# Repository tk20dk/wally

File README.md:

# Wally - CEC sniffer, sink and source emulator

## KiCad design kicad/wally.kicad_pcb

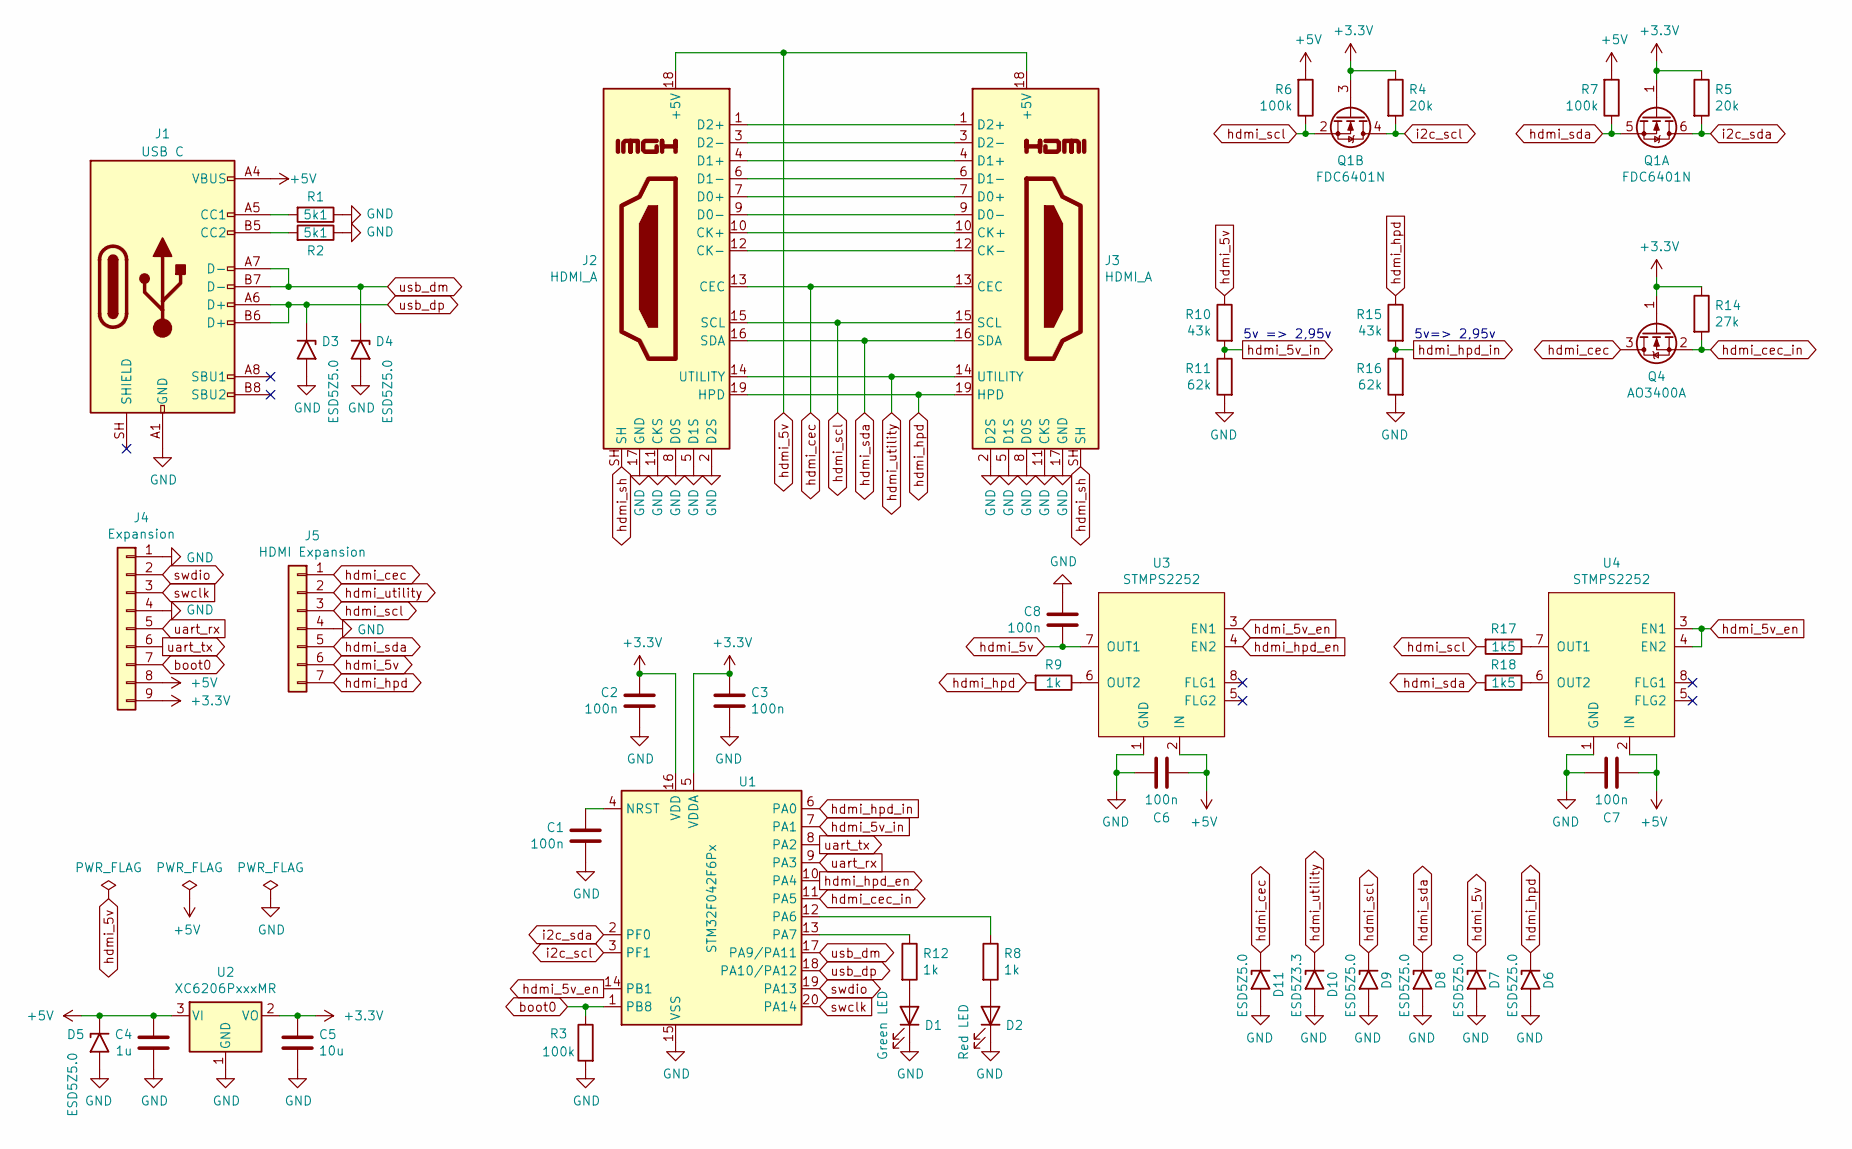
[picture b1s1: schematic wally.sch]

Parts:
C1, C2, C3, C6, C7, C8: 100n; C_0603_1608Metric
C4: 1u; C_0805_2012Metric
C5: 10u; C_0805_2012Metric
D1: Green LED; LED_0603_1608Metric
D2: Red LED; LED_0603_1608Metric
D3, D4, D5, D6, D7, D8, D9, D11: ESD5Z5.0; D_SOD-523
D10: ESD5Z3.3; D_SOD-523
J1: USB C; USB_C_Receptacle_HRO_TYPE-C-31-M-12
J2, J3: HDMI_A; HDMI_A_Male_Horizontal
J4: Expansion; PinHeader_1x09_P2.54mm_Vertical
J5: HDMI Expansion; PinHeader_1x07_P2.54mm_Vertical
Q1: FDC6401N; SuperSOT-6
Q4: AO3400A; SOT-23
R1, R2: 5k1; R_0603_1608Metric
R3, R6, R7: 100k; R_0603_1608Metric
R4, R5: 20k; R_0603_1608Metric
R8, R9, R12: 1k; R_0603_1608Metric
R10, R15: 43k; R_0603_1608Metric
R11, R16: 62k; R_0603_1608Metric
R14: 27k; R_0603_1608Metric
R17, R18: 1k5; R_0603_1608Metric
U1: STM32F042F6Px; TSSOP-20_4.4x6.5mm_P0.65mm
U2: XC6206PxxxMR; SOT-23
U3, U4: STMPS2252; MSOP-8_3x3mm_P0.65mm

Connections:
+3V3: C2.2, C3.2, C5.1, J4.9, Q1.1 (G), Q1.3 (G), Q4.1 (G), R4.1, R5.1, R14.1, U1.5 (VDDA), U1.16 (VDD), U2.2 (VO)
+5V: C4.2, C6.2, C7.2, D5.1 (A1), J1.A4 (VBUS), J1.A9 (VBUS), J1.B4 (VBUS), J1.B9 (VBUS), J4.8, R6.2, R7.2, U2.3 (VI), U3.2 (IN), U4.2 (IN)
GND: C1.1, C2.1, C3.1, C4.1, C5.2, C6.1, C7.1, C8.2, D1.1 (K), D2.1 (K), D3.2 (A2), D4.2 (A2), D5.2 (A2), D6.2 (A2), D7.2 (A2), D8.2 (A2), D9.2 (A2), D10.2 (A2), D11.2 (A2), J1.A1 (GND), J1.A12 (GND), J1.B1 (GND), J1.B12 (GND), J2.2 (D2S), J2.5 (D1S), J2.8 (D0S), J2.11 (CKS), J2.17 (GND), J3.2 (D2S), J3.5 (D1S), J3.8 (D0S), J3.11 (CKS), J3.17 (GND), J4.1, J4.4, J5.4, R1.1, R2.1, R3.2, R11.2, R16.2, U1.15 (VSS), U2.1 (GND), U3.1 (GND), U4.1 (GND)
unnamed: C1.2, U1.4 (NRST)
unnamed: D1.2 (A), R12.2
unnamed: D2.2 (A), R8.2
unnamed: J1.A5 (CC1), R1.2
unnamed: J1.B5 (CC2), R2.2
unnamed: J2.1 (D2+), J3.1 (D2+)
unnamed: J2.3 (D2-), J3.3 (D2-)
unnamed: J2.4 (D1+), J3.4 (D1+)
unnamed: J2.6 (D1-), J3.6 (D1-)
unnamed: J2.7 (D0+), J3.7 (D0+)
unnamed: J2.9 (D0-), J3.9 (D0-)
unnamed: J2.10 (CK+), J3.10 (CK+)
unnamed: J2.12 (CK-), J3.12 (CK-)
unnamed: R8.1, U1.12 (PA6)
unnamed: R9.1, U3.6 (OUT2)
unnamed: R12.1, U1.13 (PA7)
unnamed: R17.1, U4.7 (OUT1)
unnamed: R18.1, U4.6 (OUT2)
boot0: J4.7, R3.1, U1.1 (PB8)
hdmi_5v: C8.1, D7.1 (A1), J2.18 (+5V), J3.18 (+5V), J5.6, R10.1, U3.7 (OUT1)
hdmi_5v_en: U1.14 (PB1), U3.3 (EN1), U4.3 (EN1), U4.4 (EN2)
hdmi_5v_in: R10.2, R11.1, U1.7 (PA1)
hdmi_cec: D11.1 (A1), J2.13 (CEC), J3.13 (CEC), J5.1, Q4.3 (D)
hdmi_cec_in: Q4.2 (S), R14.2, U1.11 (PA5)
hdmi_hpd: D6.1 (A1), J2.19 (HPD), J3.19 (HPD), J5.7, R9.2, R15.1
hdmi_hpd_en: U1.10 (PA4), U3.4 (EN2)
hdmi_hpd_in: R15.2, R16.1, U1.6 (PA0)
hdmi_scl: D9.1 (A1), J2.15 (SCL), J3.15 (SCL), J5.3, Q1.2 (S), R6.1, R17.2
hdmi_sda: D8.1 (A1), J2.16 (SDA), J3.16 (SDA), J5.5, Q1.5 (S), R7.1, R18.2
hdmi_sh: J2.SH, J3.SH
hdmi_utility: D10.1 (A1), J2.14 (UTILITY), J3.14 (UTILITY), J5.2
i2c_scl: Q1.4 (D), R4.2, U1.3 (PF1)
i2c_sda: Q1.6 (D), R5.2, U1.2 (PF0)
swclk: J4.3, U1.20 (PA14)
swdio: J4.2, U1.19 (PA13)
uart_rx: J4.5, U1.9 (PA3)
uart_tx: J4.6, U1.8 (PA2)
usb_dm: D4.1 (A1), J1.A7 (D-), J1.B7 (D-), U1.17 (PA9/PA11)
usb_dp: D3.1 (A1), J1.A6 (D+), J1.B6 (D+), U1.18 (PA10/PA12)

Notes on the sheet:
5v => 2,95v
5v=> 2,95v

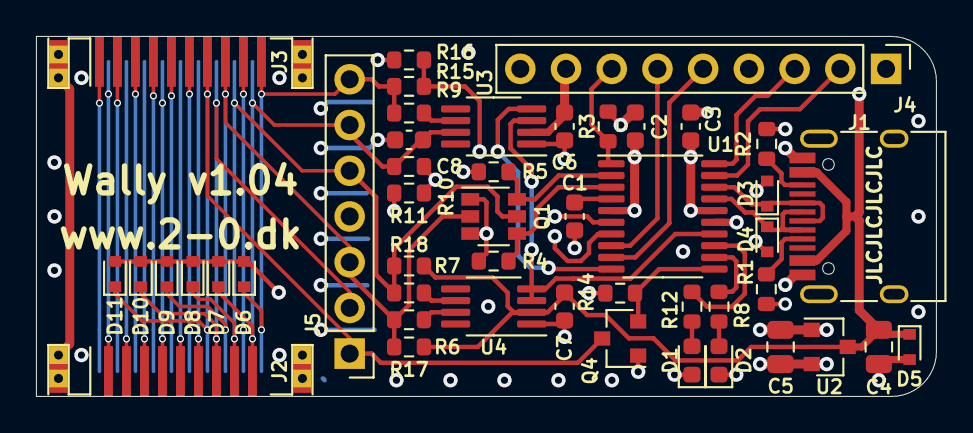
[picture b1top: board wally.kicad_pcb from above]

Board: 4 copper layers, 50.0 x 20.0 mm, 47 parts (1 on the bottom side), 42 nets.

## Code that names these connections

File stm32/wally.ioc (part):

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PA6.GPIOParameters=GPIO_Label
PB8.GPIOParameters=GPIO_Label
Mcu.UserName=STM32F042F6Px
PA3.GPIO_PuPd=GPIO_PULLUP
PA0.GPIO_Label=HDMI_5V_IN
PA2.GPIO_Speed=GPIO_SPEED_FREQ_LOW
PA11.Mode=Device
PA3.GPIOParameters=GPIO_Speed,GPIO_PuPd
PA6.GPIO_Label=LED_RED
PA3.GPIO_Speed=GPIO_SPEED_FREQ_LOW
PA2.GPIOParameters=GPIO_Speed
RCC.SYSCLKSource=RCC_SYSCLKSOURCE_HSI48
PA3.Mode=Asynchronous
PA13.Signal=SYS_SWDIO
PB8.GPIO_Label=HDMI_HPD_EN
PA12.Signal=USB_DP
PF0-OSC_IN.GPIO_PuPd=GPIO_PULLUP
PF1-OSC_OUT.GPIO_PuPd=GPIO_PULLUP
PF1-OSC_OUT.GPIOParameters=GPIO_PuPd,GPIO_Label
PA1.Signal=GPIO_Input
PA5.Signal=CEC
PF0-OSC_IN.GPIO_Label=HDMI_SDA
board=custom
PA1.GPIOParameters=GPIO_Label
PA14.Mode=Serial_Wire
PB1.GPIO_Label=LED_YELLOW
PF1-OSC_OUT.GPIO_Label=HDMI_SCL
PA1.GPIO_Label=HDMI_HPD_IN
PA4.GPIOParameters=GPIO_Label
PA13.Mode=Serial_Wire
Mcu.Name=STM32F042F6Px
PA2.Signal=USART2_TX
PA0.Signal=GPIO_Input
PA4.Signal=GPIO_Output
RCC.SYSCLKFreq_VALUE=48000000
Mcu.Package=TSSOP20
PA6.Signal=GPIO_Output
PB1.Signal=GPIO_Output
PA7.GPIO_Label=LED_GREEN
PA12.Mode=Device
PA5.GPIO_Label=HDMI_CEC_IN
PA11.Signal=USB_DM
PA14.Signal=SYS_SWCLK
PA0.GPIOParameters=GPIO_Label
PA5.GPIOParameters=GPIO_Label
PB8.Signal=GPIO_Output
PA2.Mode=Asynchronous
PF0-OSC_IN.Signal=GPIO_Input
PF0-OSC_IN.GPIOParameters=GPIO_PuPd,GPIO_Label
PA4.GPIO_Label=HDMI_5V_EN
PA7.GPIOParameters=GPIO_Label
PF1-OSC_OUT.Signal=GPIO_Input
PA3.Signal=USART2_RX
PB1.GPIOParameters=GPIO_Label
PA5.Mode=CEC_Activate
PA7.Signal=GPIO_Output

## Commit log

2021-04-11 wally_v1.00
2021-04-25 Wally v1.01
2021-05-18 Wally v1.02
2021-06-02 v1.02 board bring-up
2021-06-05 Wally v1.03
2021-07-26 new cec decoder
2021-07-27 added serial usb driver
2021-07-27 removed serial usb driver
2021-07-30 added virtual usb serial port
2021-07-31 Wally v1.04
